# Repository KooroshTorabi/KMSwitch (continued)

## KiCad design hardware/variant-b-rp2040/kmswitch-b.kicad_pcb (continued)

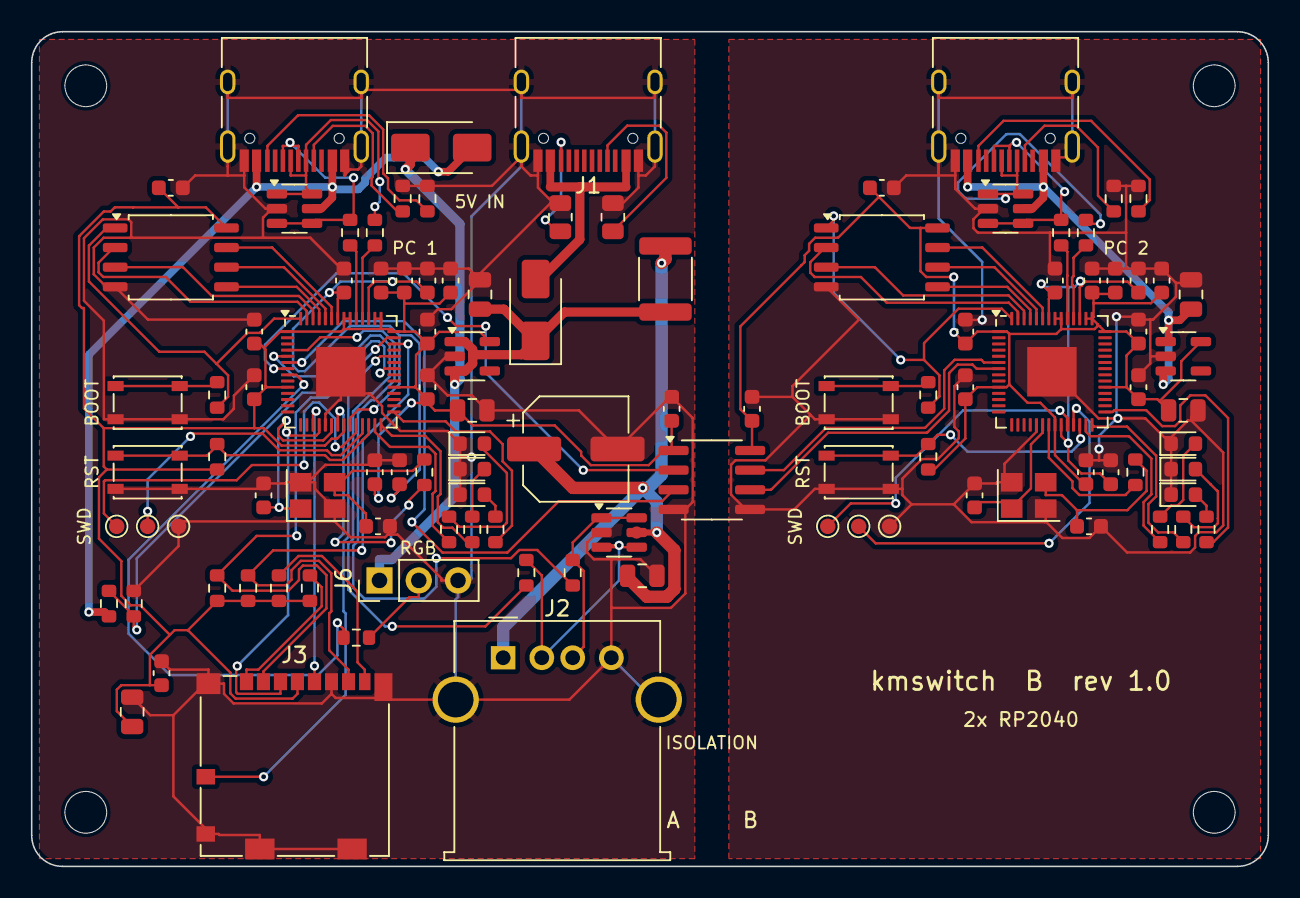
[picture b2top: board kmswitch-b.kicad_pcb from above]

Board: 2 copper layers, 80.0 x 54.0 mm, 110 parts (0 on the bottom side), 81 nets.

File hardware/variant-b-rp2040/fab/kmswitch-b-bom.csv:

Comment,Designator,Footprint,Quantity,LCSC Part #,Notes
100uF 10V,C1,CP_Elec_6.3x7.7,1,C294520,"VT1V101M-CRE77, 100uF 35V 6.3x7.7 (higher voltage is fine)"
100nF,C2,C_0805_2012Metric,1,C49678,
100nF,"C3,C4,C6,C14,C15,C16,C17,C18,C19,C20,C21,C24,C25,C54,C55,C56,C57,C58,C59,C60,C61,C64,C65",C_0603_1608Metric,23,C14663,
10uF,"C5,C26,C27,C66,C67",C_0805_2012Metric,5,C15850,
15pF,"C11,C12,C51,C52",C_0603_1608Metric,4,C1644,
1uF,"C22,C23,C62,C63",C_0603_1608Metric,4,C15849,
SS34,"D2,D3",D_SMA,2,C8678,
red,"D37,D77",LED_0603_1608Metric,2,C2286,KT-0603R
green,"D38,D78",LED_0603_1608Metric,2,C12624,KT-0603G
blue,"D39,D79",LED_0603_1608Metric,2,C2288,KT-0603B
2A hold (1812),F1,Fuse_1812_4532Metric,1,C545213,"SMD1812P200TF/16, 2A hold 16V"
USB-C 5V IN,J1,USB_C_Receptacle_HRO_TYPE-C-31-M-12,1,C165948,
USB-A host (hub/keyboard),J2,USB_A_Molex_67643_Horizontal,1,n/a,"Molex 67643-0910 through-hole (Mouser/DigiKey/TME), hand-solder"
104031-0811,J3,microSD_HC_Molex_104031-0811,1,C585350,
USB-C to PC 1,J4,USB_C_Receptacle_HRO_TYPE-C-31-M-12,1,C165948,
USB-C to PC 2,J5,USB_C_Receptacle_HRO_TYPE-C-31-M-12,1,C165948,
RGB LED (WS2812): 5V DIN GND,J6,PinHeader_1x03_P2.54mm_Vertical,1,n/a,"optional 3-pin header, not assembled (DNP)"
5.1k,"R1,R2",R_0805_2012Metric,2,C27834,
22R,"R3,R4",R_0603_1608Metric,2,C23345,
10k,"R5,R6,R7,R8,R32,R42,R72",R_0603_1608Metric,7,C25804,
330R,"R9,R38,R78",R_0603_1608Metric,3,C23138,
1k,"R13,R30,R37,R53,R70,R77",R_0603_1608Metric,6,C21190,
27R,"R28,R29,R68,R69",R_0603_1608Metric,4,C25190,0603WAF270JT5E
100R,"R39,R79",R_0603_1608Metric,2,C22775,0603WAF1000T5E
5.1k,"R40,R41,R44,R45",R_0603_1608Metric,4,C23186,
20k,R43,R_0603_1608Metric,1,C4184,
BOOTSEL,"SW31,SW71",SW_SPST_PTS810,2,C116501,PTS810SJM250SMTRLFS
RESET,"SW33,SW73",SW_SPST_PTS810,2,C116501,PTS810SJM250SMTRLFS
CA-IS3721HS,U3,SOIC-8_3.9x4.9mm_P1.27mm,1,C428884,
USBLC6-2SC6,"U4,U5,U6",SOT-23-6,3,C7519,
RP2040,"U10,U50",QFN-56-1EP_7x7mm_P0.4mm_EP3.2x3.2mm,2,C2040,
W25Q16JVSSIQ (2 MB),"U11,U51",SOIC-8_5.23x5.23mm_P1.27mm,2,C131024,
AP2112K-3.3,"U12,U52",SOT-23-5,2,C51118,
12MHz,"Y10,Y50",Crystal_SMD_3225-4Pin_3.2x2.5mm,2,C9002,

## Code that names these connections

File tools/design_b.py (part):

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

def rp2040(ref, s, gpio, pcb):
    """s = side suffix (A/B); gpio = {'GPIO2': net, ...}"""
    pins = {num: None for num in _rp.values()}
    def setn(name, net):
        pins[_rp[name]] = net
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        C(nx('TP'), 'Connector:TestPoint', 'SWCLK', 'TestPoint:TestPoint_Pad_D1.0mm', {'1': 'SWCLK_' + s}, at(-14.5, 10.0)),
        C(nx('TP'), 'Connector:TestPoint', 'SWDIO', 'TestPoint:TestPoint_Pad_D1.0mm', {'1': 'SWDIO_' + s}, at(-12.5, 10.0)),
        C(nx('TP'), 'Connector:TestPoint', 'GND', 'TestPoint:TestPoint_Pad_D1.0mm', {'1': G}, at(-10.5, 10.0)),
        # status LED: three 0603 LEDs (red / green / blue) on GPIO16 / 17 / 18, under the case window
        C('D%d' % (n0 + 27), 'Device:LED', 'red', 'LED_SMD:LED_0603_1608Metric', {'1': G, '2': 'LED_RA_' + s}, at(8.5, 4.65)),
        C('D%d' % (n0 + 28), 'Device:LED', 'green', 'LED_SMD:LED_0603_1608Metric', {'1': G, '2': 'LED_GA_' + s}, at(8.5, 6.3)),
        C('D%d' % (n0 + 29), 'Device:LED', 'blue', 'LED_SMD:LED_0603_1608Metric', {'1': G, '2': 'LED_BA_' + s}, at(8.5, 7.95)),
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    return c


gA = {'GPIO2': 'USBH_DP', 'GPIO3': 'USBH_DM', 'GPIO4': 'UART_TX_A', 'GPIO5': 'UART_RX_A',
      'GPIO14': 'SD_SCK', 'GPIO15': 'SD_MOSI', 'GPIO28': 'SD_MISO', 'GPIO29': 'SD_CS', 'GPIO26': 'SD_DET',
      'GPIO24': 'VBUS_SENSE_A', 'GPIO6': 'RGB_DATA', 'GPIO16': 'LED_R_A', 'GPIO17': 'LED_G_A', 'GPIO18': 'LED_B_A'}
gB = {'GPIO4': 'UART_TX_B', 'GPIO5': 'UART_RX_B', 'GPIO16': 'LED_R_B', 'GPIO17': 'LED_G_B', 'GPIO18': 'LED_B_B'}

coreA = core('A', 20, 22, 10, '+5V_SYS_A', gA)
coreB = core('B', 66, 22, 50, 'VBUS_PC2', gB)
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    ('Power input - 5 V adapter (J1) OR-ed with PC 1 VBUS (D2/D3)', _pick(('J1', 'R1', 'R2', 'D2', 'D3', 'F1', 'C1', 'C2')),
     'D2/D3 make the adapter and PC 1 share the load without ever back-feeding each other.\n'
     'Works without the adapter as long as PC 1 is on; with the adapter the keyboard works while PC 1 is off.'),
    ('PC 1 USB-C (device) + VBUS sense on GPIO24', _pick(('J4', 'U5', 'R40', 'R41', 'R42', 'R43')), None),
    ('MCU-A - RP2040 (USB host, router, microSD)', coreA,
     'GPIO2/3 = PIO-USB host, GPIO4/5 = UART1, GPIO14/15/28/29 = SPI1 + CS, GPIO26 = card detect, GPIO16/17/18 = status LED red/green/blue.'),
    ('USB host port (keyboard, mouse, dongle or hub)', _pick(('J2', 'U4', 'R3', 'R4')), None),
    ('microSD - shared drive', _pick(('J3', 'R5', 'R6', 'R7', 'R8', 'C5', 'C6')), None),
    ('Galvanic isolation (GND_A and GND_B never meet)', _pick(('U3', 'C3', 'C4')),
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    ('PC 2 USB-C (device, powers side B)', _pick(('J5', 'U6', 'R44', 'R45')), None),
    ('MCU-B - RP2040', coreB, None),
    ('Optional RGB LED header (WS2812/SK6812): 5V, DIN, GND', _pick(('J6', 'R9')),
     'Data from GPIO6 through R9 (same pin as variant A).'),
    ('Mechanical', _pick(('H1', 'H2', 'H3', 'H4')), None),
]

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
